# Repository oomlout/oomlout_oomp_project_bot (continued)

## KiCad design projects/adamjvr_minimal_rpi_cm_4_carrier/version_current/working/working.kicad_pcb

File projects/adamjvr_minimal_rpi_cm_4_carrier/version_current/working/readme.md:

# Minimal-RPi-CM-4-Carrier by adamjvr  
This is a harvested standardized copy of a project from github.  
The original project can be found at:  
https://github.com/adamjvr/Minimal-RPi-CM-4-Carrier  
Please consult that link for additional, details, files, and license information.  
Note: It was auto harvested and if the original repo had more than one board file or anything out of the ordinary the files here are likely not representative.

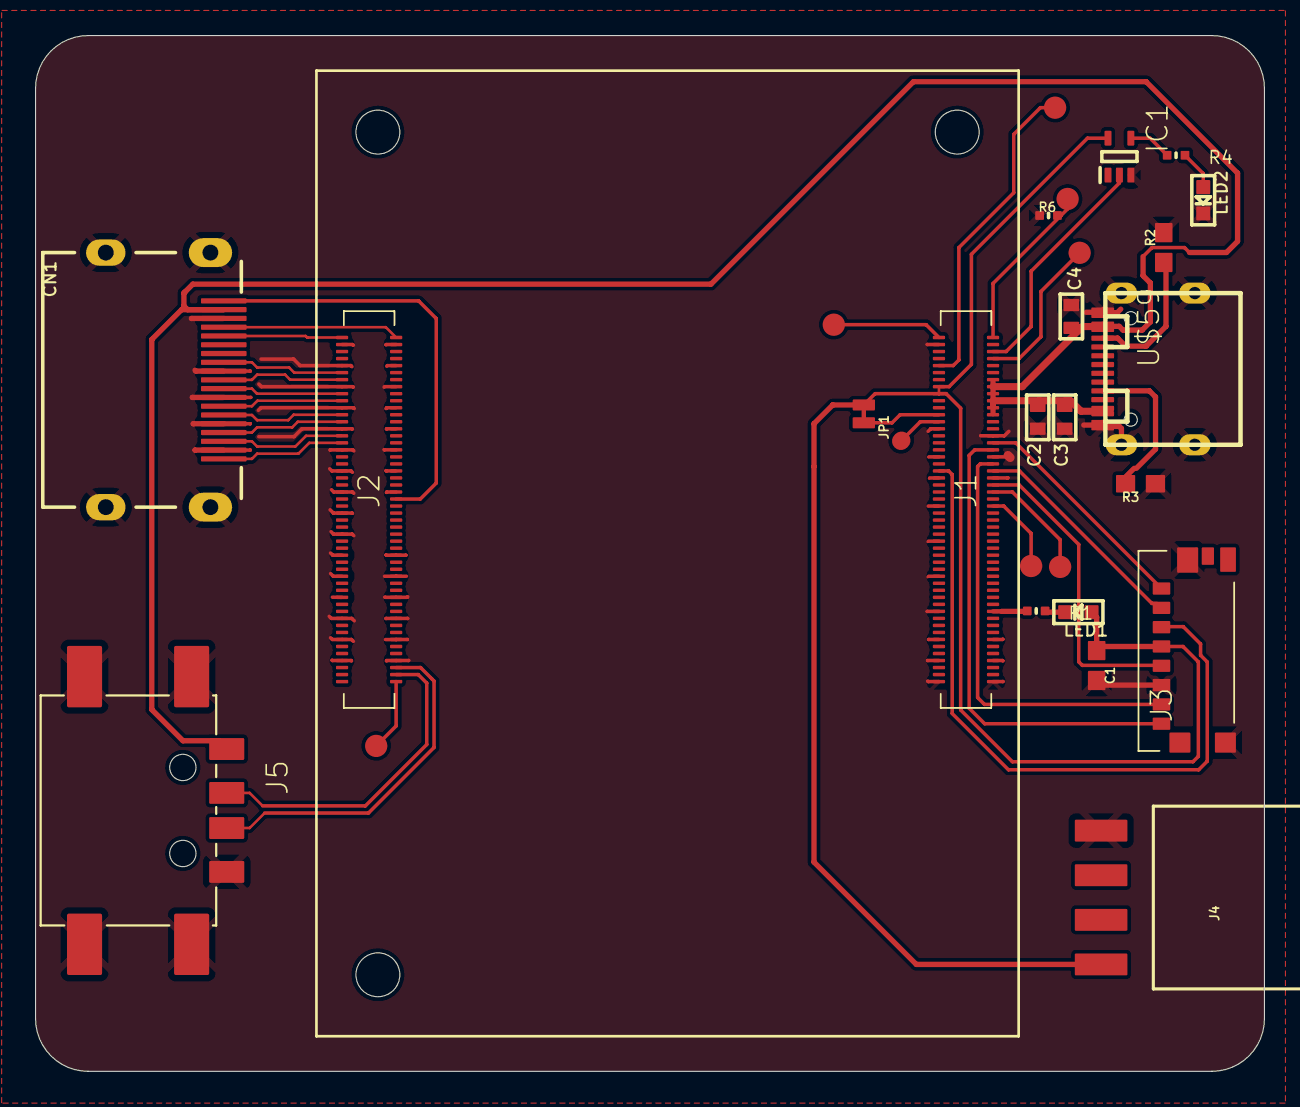
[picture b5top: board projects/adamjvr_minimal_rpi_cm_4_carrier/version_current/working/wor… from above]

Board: 2 copper layers, 70.0 x 59.0 mm, 30 parts (0 on the bottom side), 38 nets.

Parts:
@HOLE0, @HOLE1, @HOLE2: (no value)
C1: 10uF; 0603
C2, C3, C4: 0402
CN1: HDMI_MOLEX_47151-0001
IC1: MC74VHC1G14DFT1G; SOT65P210X110-5N
J1: P1-100; DF40C100DS04V51
J2: P101-200; DF40C100DS04V51
J3: 47571-0001
J4: 1X04_SMD_RA_FEMALE
J5: 629104190121
JP1: JUMPER-SMT_2_NC_TRACE_NO-SILK; SMT-JUMPER_2_NC_TRACE_NO-SILK
LED1, LED2: CHIPLED_0603
R1, R4: 1k; _0402MP
R2, R3: 5.1k; 0603
R6: 10k; _0402MP
TP1, TP2, TP3, TP4, TP5, TP6, TP7: TEST-POINT3X5; PAD.03X.05
U$59: TYPE-C-31-M-12; USB-TYPE-C_16PIN-MALE-TYPE-C-31-M-12

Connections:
1.8V: J1.88, J1.90
3.3V: C1.1, IC1.5, J1.84, J1.86, J3.P4, J4.1, JP1.1, LED1.A
5.0V: C2.1, C3.1, C4.1, CN1.18, J1.77, J1.79, J1.81, J1.83, J1.85, J1.87, J5.1, U$59.A4, U$59.A9, U$59.B4, U$59.B9
A0/CC2: R3.2, U$59.A5
A3/CC1: R2.1, U$59.B5
GLOBAL_EN: J1.99, R6.2, TP3.P$1
GND: C1.2, C2.2, C3.2, C4.2, CN1.2, CN1.5, CN1.8, CN1.11, CN1.17, CN1.P$1, CN1.P$2, CN1.P$3, CN1.P$4, IC1.3, J1.1, J1.2, J1.7, J1.8, J1.13, J1.14, J1.22, J1.23, J1.32, J1.33, J1.42, J1.43, J1.52, J1.53, J1.59, J1.60, J1.65, J1.66, J1.71, J1.74, J1.98, J2.7, J2.8, J2.13, J2.14, J2.19, J2.20, J2.25, J2.26, J2.31, J2.32, J2.37, J2.38, J2.44, J2.50, J2.55, J2.56, J2.61, J2.62, J2.67, J2.68, J2.73, J2.74, J2.79, J2.80, J2.85, J2.86, J2.91, J2.92, J2.97, J2.98, J3.G1, J3.G2, J3.G3, J3.P6, J4.4, J5.4, J5.SHELL, J5.SHELL1, J5.SHELL2, J5.SHELL3, LED2.C, R2.2, R3.1, R6.1, U$59.0, U$59.0-1, U$59.0-2, U$59.0-3, U$59.A1, U$59.A12, U$59.B1, U$59.B12
GPIO14: J1.55, J4.3, TP7.P$1
GPIO15: J1.51, J4.2, TP6.P$1
GPIO_VREF: J1.78, JP1.2
HDMI0_CK_N: CN1.12, J2.90
HDMI0_CK_P: CN1.10, J2.88
HDMI0_D0_N: CN1.9, J2.84
HDMI0_D0_P: CN1.7, J2.82
HDMI0_D1_N: CN1.6, J2.78
HDMI0_D1_P: CN1.4, J2.76
HDMI0_D2_N: CN1.3, J2.72
HDMI0_D2_P: CN1.1, J2.70
HDMI0_HOTPLUG: CN1.19, J2.53
HDMI0_SCL: CN1.15, J2.100
HDMI0_SDA: CN1.16, J2.99
unnamed: LED1.C, R1.2
unnamed: IC1.4, R4.1
unnamed: LED2.A, R4.2
N_EXTRST: J1.100, TP2.P$1
N_PWR_LED: IC1.2, J1.95
N_RPIBOOT: J1.93, TP4.P$1
PI_NLED_ACTIVITY: J1.21, R1.1
RUN_PG: J1.92, TP1.P$1
SD_CLK: J1.57, J3.P5
SD_CMD: J1.62, J3.P3
SD_DAT0: J1.63, J3.P7
SD_DAT1: J1.67, J3.P8
SD_DAT2: J1.69, J3.P1
SD_DAT3: J1.61, J3.P2
USB2_N: J2.3, J5.2
USB2_P: J2.5, J5.3
USBOTG_ID: J2.1, TP5.P$1

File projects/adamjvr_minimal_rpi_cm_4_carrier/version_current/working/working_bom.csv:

"Id";"Designator";"Footprint";"Quantity";"Designation";"Supplier and ref";
1;"R6";"_0402MP";1;"10k";;;
2;"R3,R2";"0603";2;"5.1k";;;
3;"J1";"DF40C100DS04V51";1;"P1-100";;;
4;"CN1";"HDMI_MOLEX_47151-0001";1;"";;;
5;"@HOLE0,@HOLE2,@HOLE1";"";3;"";;;
6;"R4,R1";"_0402MP";2;"1k";;;
7;"TP4,TP2,TP1,TP5,TP7,TP6,TP3";"PAD.03X.05";7;"TEST-POINT3X5";;;
8;"J3";"47571-0001";1;"47571-0001";;;
9;"IC1";"SOT65P210X110-5N";1;"MC74VHC1G14DFT1G";;;
10;"J2";"DF40C100DS04V51";1;"P101-200";;;
11;"C4,C2,C3";"0402";3;"";;;
12;"U$59";"USB-TYPE-C_16PIN-MALE-TYPE-C-31-M-12";1;"TYPE-C-31-M-12";;;
13;"LED2,LED1";"CHIPLED_0603";2;"";;;
14;"JP1";"SMT-JUMPER_2_NC_TRACE_NO-SILK";1;"JUMPER-SMT_2_NC_TRACE_NO-SILK";;;
15;"J4";"1X04_SMD_RA_FEMALE";1;"";;;
16;"J5";"629104190121";1;"";;;
17;"C1";"0603";1;"10uF";;;

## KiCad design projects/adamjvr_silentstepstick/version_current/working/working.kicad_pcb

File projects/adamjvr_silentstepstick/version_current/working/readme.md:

# OOMP Project  
## SilentStepStick  by adamjvr  
  
oomp key: oomp_projects_flat_adamjvr_silentstepstick  
(snippet of original readme)  
  
- SilentStepStick  
The Silent-Step-Stick is a Stepper Motor Driver Board for 2-Phase Motors based on [Trinamic](https://www.trinamic.com) Motor Drivers.  
  
* Hardware compatible with [StepStick](https://reprap.org/wiki/StepStick) and [Pololu A4988](https://www.pololu.com/product/1182)  
* [Trinamic](https://www.trinamic.com) stepper motor driver (chopper drive / constant current drive) with  
  * Automatic standby current reduction  
  * **microPlyer** - microstep interpolator for increased smoothness of microstepping  
  * **stealthChop** - for quiet operation and smooth motion  
  * **spreadCycle** - highly dynamic motor control chopper  
* Open-Source and released under the [Creative Commons Attribution Share-Alike License](https://creativecommons.org/licenses/by-sa/4.0/).  
* **[Documentation on learn.watterott.com](https://learn.watterott.com)**  
  
  full source readme at [readme_src.md](readme_src.md)  
  
source repo at: [https://github.com/adamjvr/SilentStepStick](https://github.com/adamjvr/SilentStepStick)  
## Board  

## Schematic  

[schematic pdf](working_schematic.pdf)  
## Images

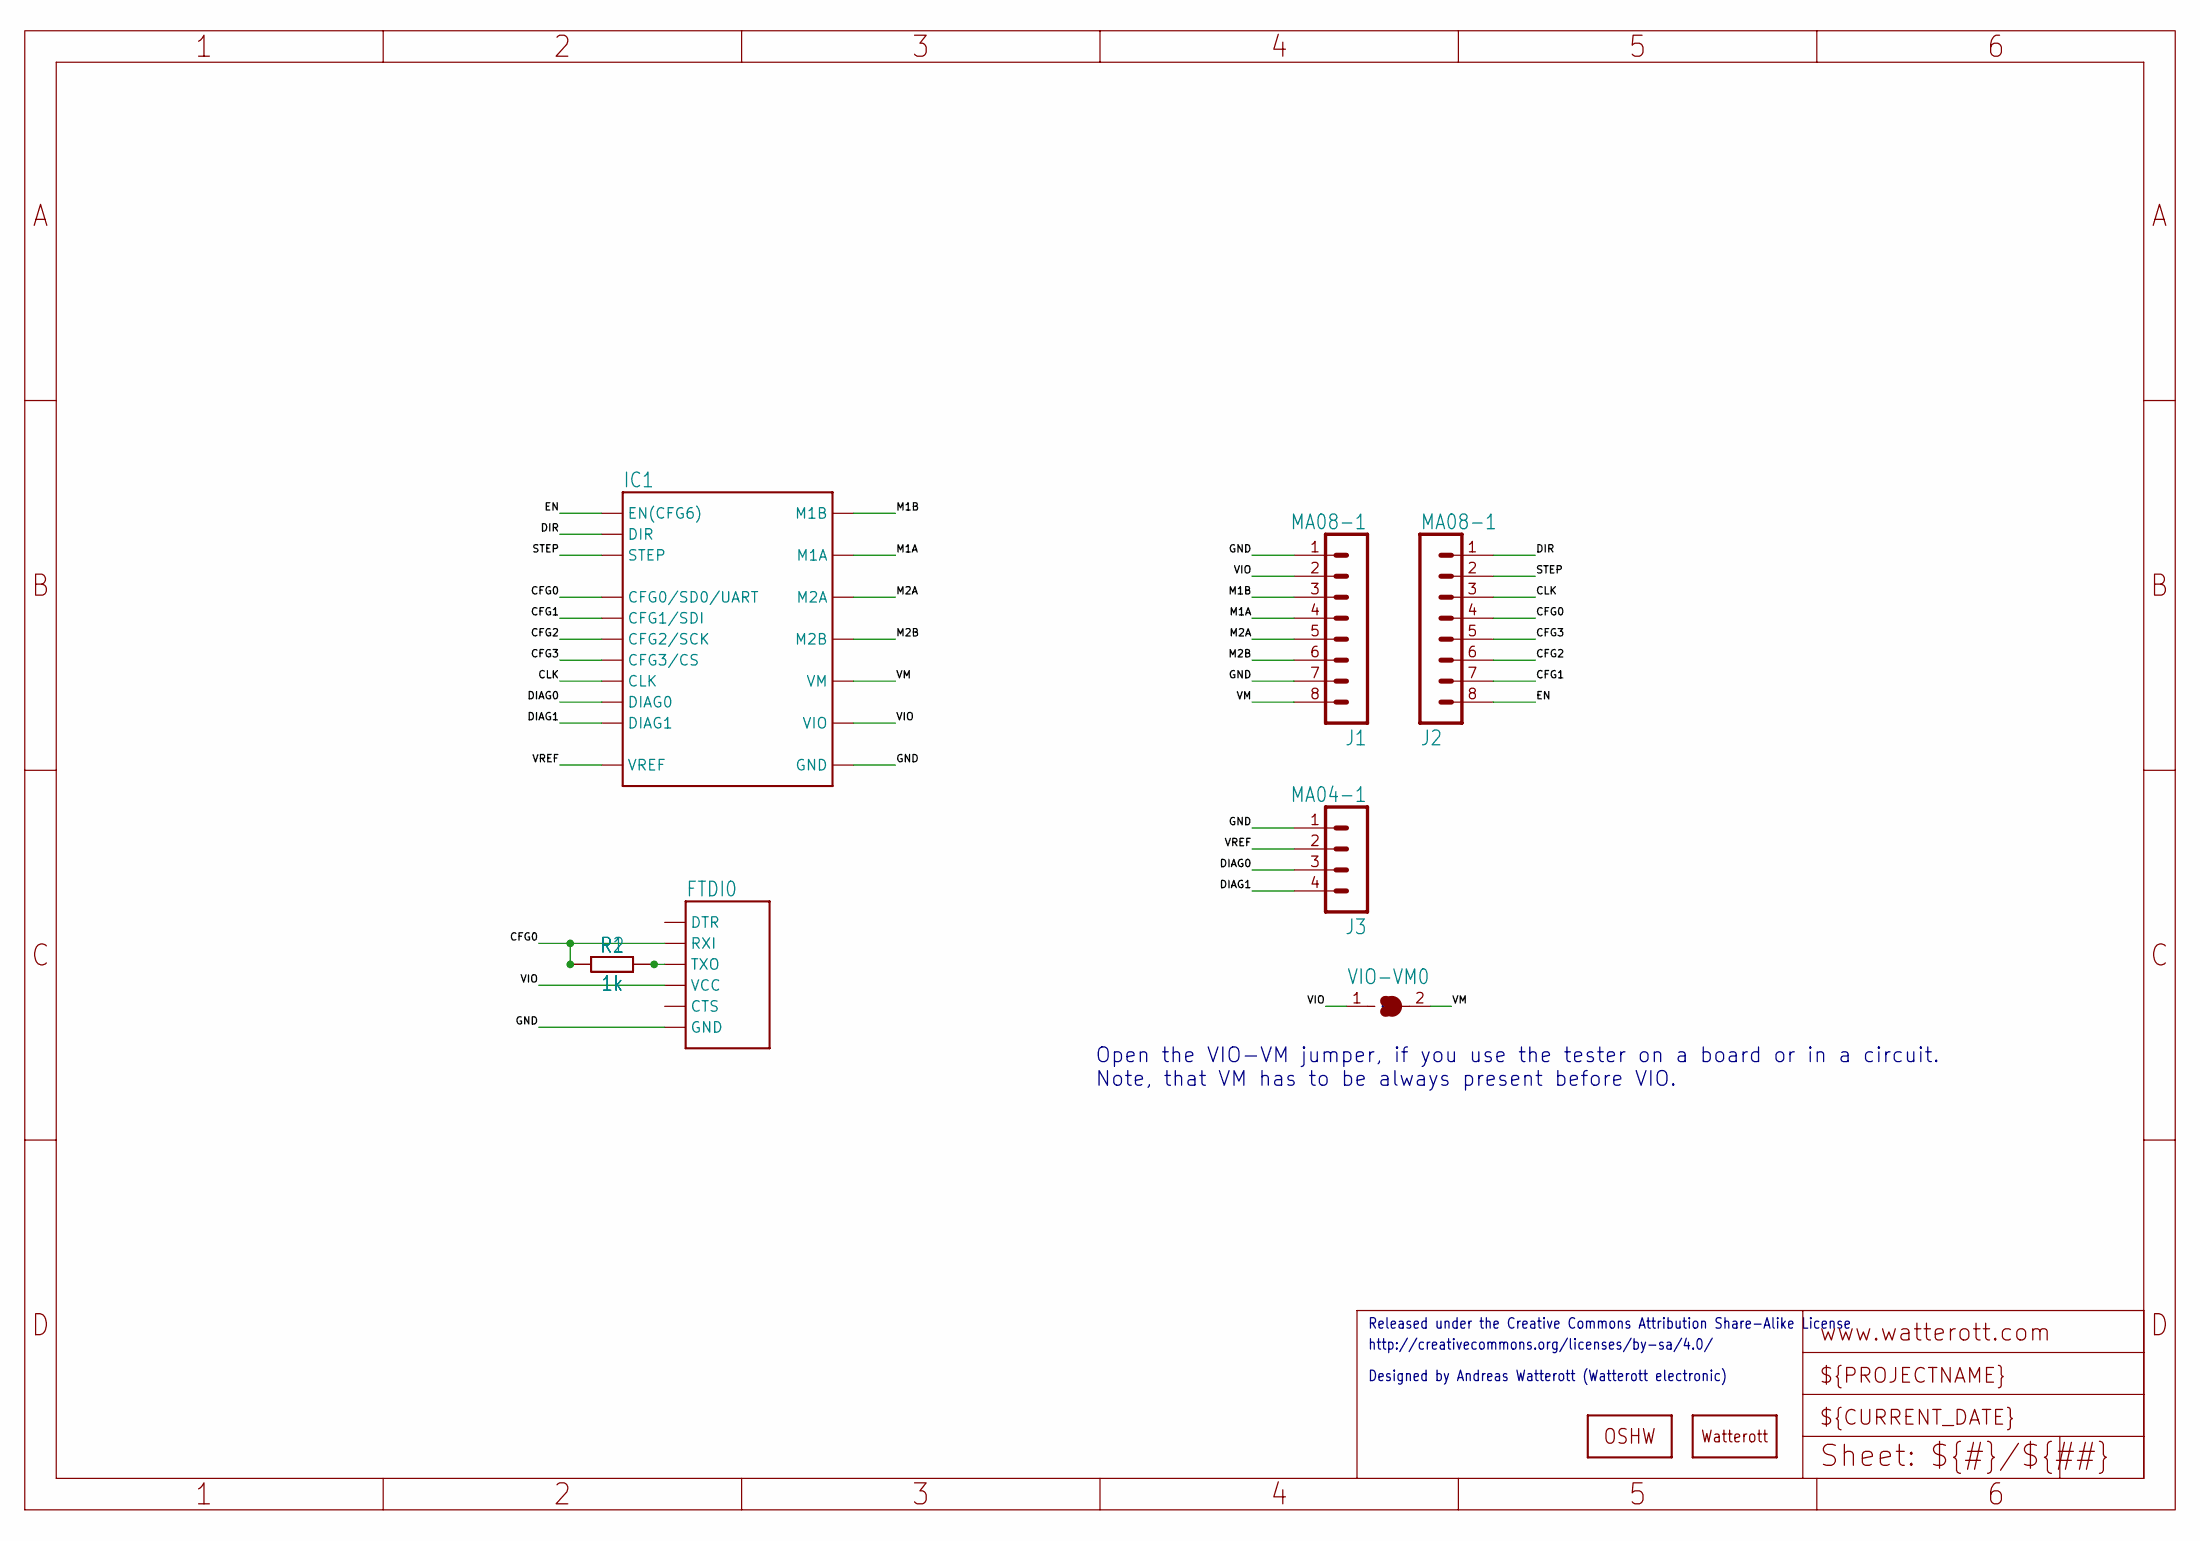
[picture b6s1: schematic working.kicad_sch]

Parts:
FTDI0: FTDI
IC1: STEPSTICK-TP; STEPSTICK_TP
J1, J2: MA08-1
J3: MA04-1
LOGO1: OSHW_LOGOX0070; OSHW_6X70
LOGO2: LOGO-S_PLACE_S; SPARK_TPLACE_S
R1: 1k; R0207_7
R2: 1k; C0805
VIO-VM0: JUMPER2-0603-NC; JUMPER2-0603_NC

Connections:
CFG0: FTDI0.5-RXI (RXI), IC1.NC/CFG0 (CFG0/SD0/UART), J2.4, R1.1, R2.1
CFG1: IC1.CFG1 (CFG1/SDI), J2.7
CFG2: IC1.CFG2 (CFG2/SCK), J2.6
CFG3: IC1.CFG3 (CFG3/CS), J2.5
CLK: IC1.NC/CLK (CLK), J2.3
DIAG0: IC1.DIAG0, J3.3
DIAG1: IC1.DIAG1, J3.4
DIR: IC1.DIR, J2.1
EN: IC1.EN (EN(CFG6)), J2.8
GND: FTDI0.1-GND (GND), IC1.GND@1 (GND), IC1.GND@2 (GND), J1.1, J1.7, J3.1
M1A: IC1.M1A, J1.4
M1B: IC1.M1B, J1.3
M2A: IC1.M2A, J1.5
M2B: IC1.M2B, J1.6
STEP: IC1.STEP, J2.2
TX: FTDI0.4-TXO (TXO), R1.2, R2.2
VIO: FTDI0.3-VCC (VCC), IC1.VIO, J1.2, VIO-VM0.1
VM: IC1.VM, J1.8, VIO-VM0.2
VREF: IC1.VREF, J3.2

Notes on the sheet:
Open the VIO-VM jumper, if you use the tester on a board or in a circuit. Note, that VM has to be always present before VIO.
http://creativecommons.org/licenses/by-sa/4.0/
Released under the Creative Commons Attribution Share-Alike License
Designed by Andreas Watterott (Watterott electronic)

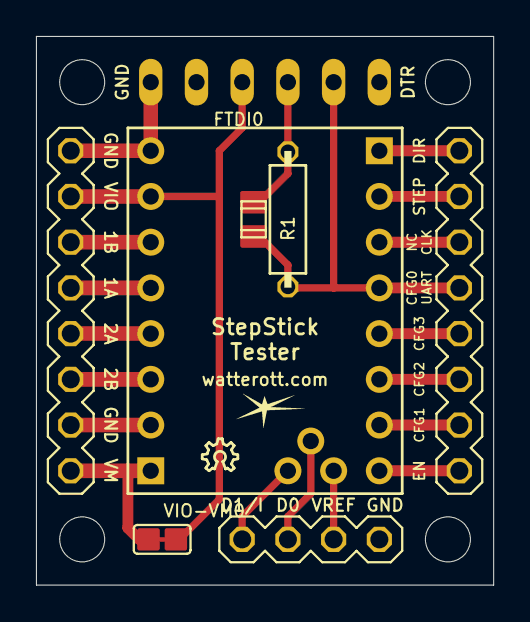
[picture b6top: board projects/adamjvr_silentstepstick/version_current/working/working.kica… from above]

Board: 2 copper layers, 25.4 x 30.5 mm, 14 parts (0 on the bottom side), 19 nets.

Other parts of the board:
@HOLE0, @HOLE1, @HOLE2, @HOLE3: (no value)

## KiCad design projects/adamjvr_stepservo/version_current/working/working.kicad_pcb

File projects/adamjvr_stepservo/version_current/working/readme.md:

# OOMP Project  
## StepServo  by adamjvr  
  
oomp key: oomp_projects_flat_adamjvr_stepservo  
(snippet of original readme)  
  
- StepServo  
  
Check out the wiki here: http://reprap.org/wiki/StepServo (under construction)  
  
A single channel step/direction/enable/endstop to DC quadrature encoder converter for use with 3D printers or CNC machines. So, basically, a single channel version of my other board, RAMPSSB (https://github.com/SZiv/RAMPSSB), and many of the rules that apply there, apply here. The firmware is identical.  
  
Uses an L298N DC motor driver stacked on standoffs as a driver, and an Arduino Pro Micro as a processor. Designed to need only an arduino Pro Micro, a L298N, some standoffs, an LED, a resistor, a 3mm terminal block, and a bunch of header. Can be assembled easily on your own.  
  
  full source readme at [readme_src.md](readme_src.md)  
  
source repo at: [https://github.com/adamjvr/StepServo](https://github.com/adamjvr/StepServo)  
## Board  

## Schematic  

[schematic pdf](working_schematic.pdf)  
## Images

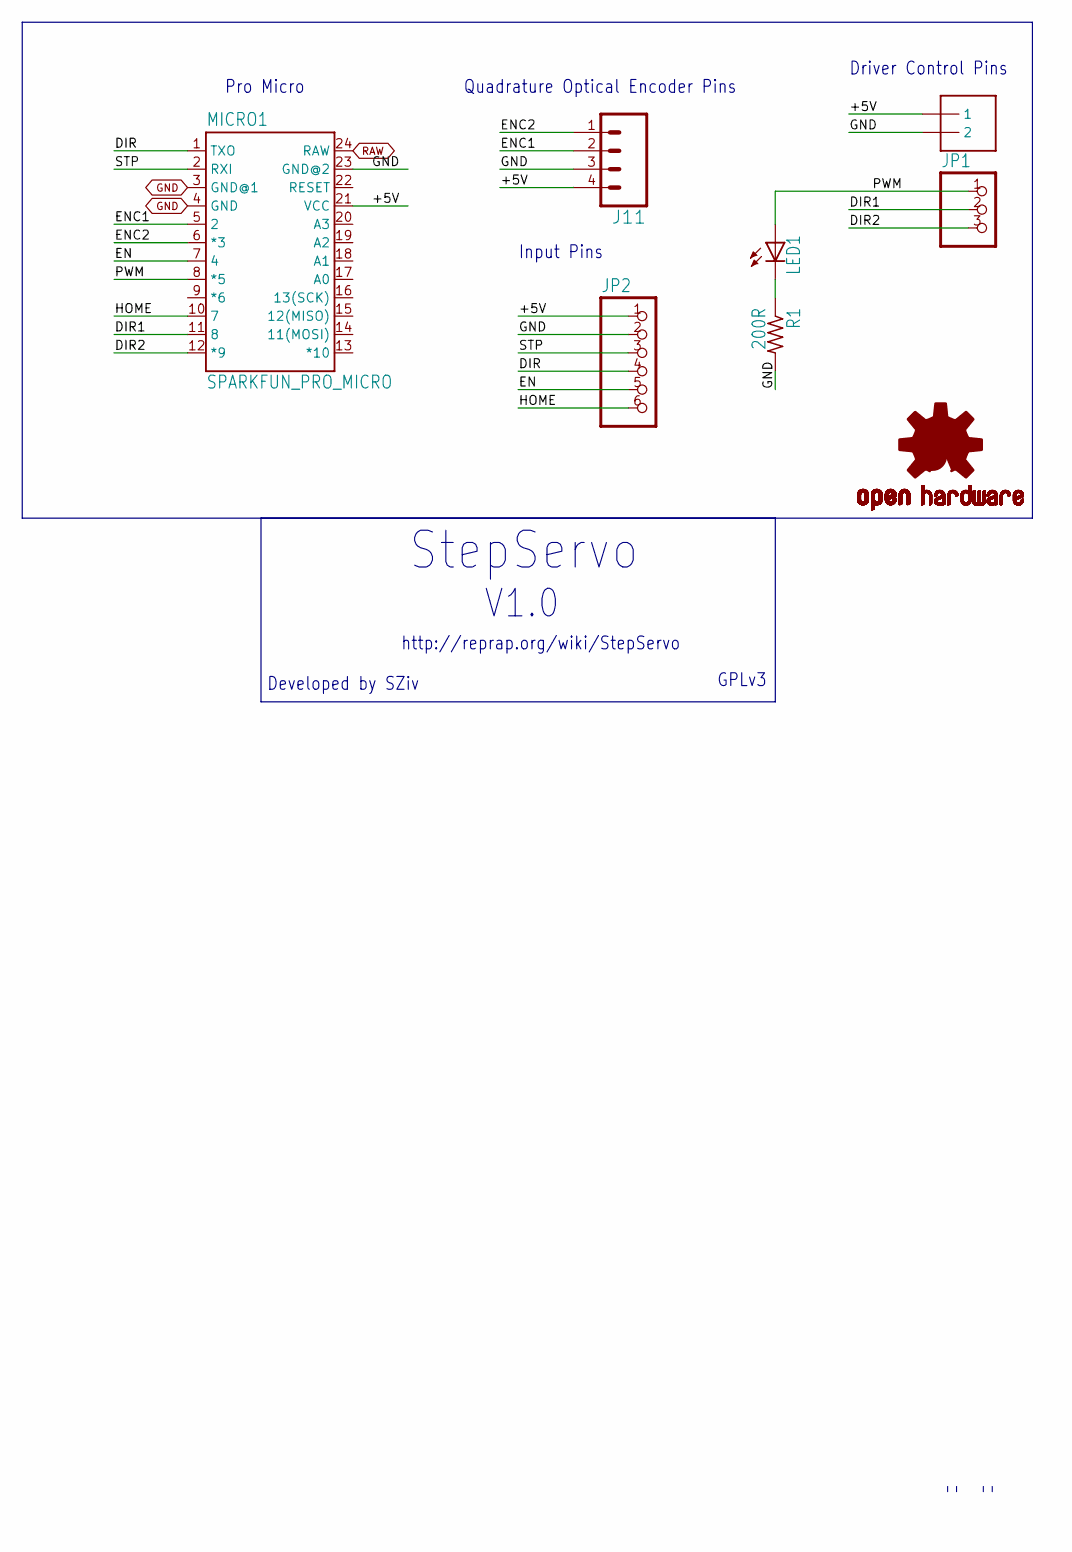
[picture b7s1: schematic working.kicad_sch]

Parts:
J2: 1X2-3.5MM
J11: CONN_04; 1X04
JP1: PINHD-1X3; 1X03
JP2: PINHD-1X6; 1X06
LED1: LED3MM
LOGO1: OSHW-LOGOL; OSHW-LOGO-L
MICRO1: SPARKFUN_PRO_MICRO
R1: 200R; 0207_7

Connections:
+5V: J2.1, J11.4, JP2.1, MICRO1.21 (VCC)
DIR: JP2.4, MICRO1.1 (TXO)
DIR1: JP1.2, MICRO1.11 (8)
DIR2: JP1.3, MICRO1.12 (*9)
EN: JP2.5, MICRO1.7 (4)
ENC1: J11.2, MICRO1.5 (2)
ENC2: J11.1, MICRO1.6 (*3)
GND: J2.2, J11.3, JP2.2, MICRO1.3 (GND@1), MICRO1.4 (GND), MICRO1.23 (GND@2), R1.2
HOME: JP2.6, MICRO1.10 (7)
unnamed: LED1.K (C), R1.1
PWM: JP1.1, LED1.A, MICRO1.8 (*5)
RAW: MICRO1.24 (RAW)
STP: JP2.3, MICRO1.2 (RXI)

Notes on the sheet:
Quadrature Optical Encoder Pins
V1.0
http://reprap.org/wiki/StepServo
Input Pins
Driver Control Pins
GPLv3
Developed by SZiv
" "
Pro Micro
StepServo

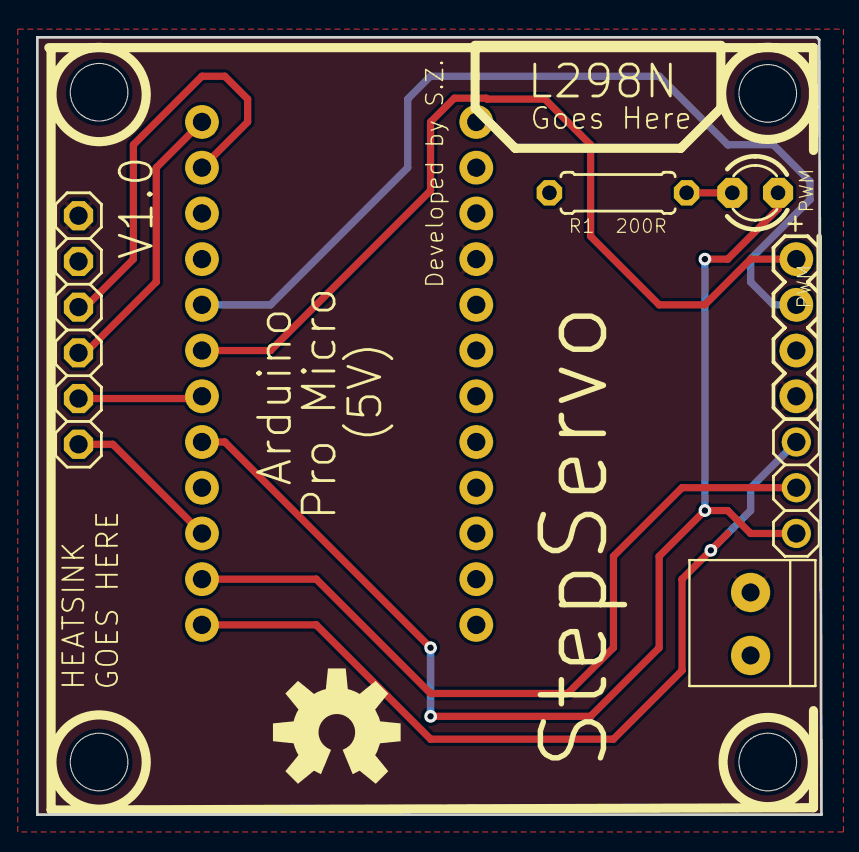
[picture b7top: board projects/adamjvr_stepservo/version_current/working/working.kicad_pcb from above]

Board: 2 copper layers, 43.6 x 43.2 mm, 12 parts (0 on the bottom side), 12 nets.

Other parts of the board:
@HOLE0, @HOLE1, @HOLE2, @HOLE3: (no value)

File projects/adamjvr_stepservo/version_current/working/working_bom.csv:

"Id";"Designator";"Footprint";"Quantity";"Designation";"Supplier and ref";
1;"LED1";"LED3MM";1;"";;;
2;"JP1";"1X03";1;"";;;
3;"LOGO1";"OSHW-LOGO-L";1;"OSHW-LOGOL";;;
4;"@HOLE3,@HOLE1,@HOLE2,@HOLE0";"";4;"";;;
5;"JP2";"1X06";1;"";;;
6;"J11";"1X04";1;"";;;
7;"R1";"0207_7";1;"200R";;;
8;"MICRO1";"SPARKFUN_PRO_MICRO";1;"SPARKFUN_PRO_MICRO";;;
9;"J2";"1X2-3.5MM";1;"1X2-3.5MM";;;

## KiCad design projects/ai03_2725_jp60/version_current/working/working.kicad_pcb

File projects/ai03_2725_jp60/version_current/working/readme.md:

# JP60 by ai03-2725  
This is a harvested standardized copy of a project from github.  
The original project can be found at:  
https://github.com/ai03-2725/JP60  
Please consult that link for additional, details, files, and license information.  
Note: It was auto harvested and if the original repo had more than one board file or anything out of the ordinary the files here are likely not representative.

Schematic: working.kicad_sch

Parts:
D1, D2, D3, D4, D5, D6, D7, D8, D9, D10, D11, D12, D13, D14, D15, D16, D17, D18, D19, D20, D21, D22, D23, D24, D25, D26, D27, D28, D29, D30, D31, D33, D34, D35, D36, D38, D39, D40, D41, D42, D44, D45, D46, D47, D49, D50, D51, D52, D54, D55, D56, D57, D59, D60, D61, D62, D63, D65, D66, D67, D70, D71, D72, D74: SOD-123; D_SOD-123
K_#0_1, K_#1, K_#2, K_#3, K_#4, K_#5, K_#6, K_#7, K_#8, K_#9: MX-NoLED; MXOnly-1U-Hotswap
K_'1: MX-NoLED; MXOnly-1U-Hotswap
K_,1: MX-NoLED; MXOnly-1U-Hotswap
K_-1: MX-NoLED; MXOnly-1U-Hotswap
K_.1: MX-NoLED; MXOnly-1U-Hotswap
K_/1: MX-NoLED; MXOnly-1U-Hotswap
K_;1: MX-NoLED; MXOnly-1U-Hotswap
K_=1: MX-NoLED; MXOnly-1U-Hotswap
K_A1: MX-NoLED; MXOnly-1U-Hotswap
K_B1: MX-NoLED; MXOnly-1U-Hotswap
K_C1: MX-NoLED; MXOnly-1U-Hotswap
K_CAPS1: MX-LED; MXOnly-1.75U-Hotswap
K_D1: MX-NoLED; MXOnly-1U-Hotswap
K_E1: MX-NoLED; MXOnly-1U-Hotswap
K_ENTER1: MX-NoLED; MXOnly-ISO-ROTATED-Hotswap
K_ESC1: MX-NoLED; MXOnly-1U-Hotswap
K_F1: MX-NoLED; MXOnly-1U-Hotswap
K_G1: MX-NoLED; MXOnly-1U-Hotswap
K_H1: MX-NoLED; MXOnly-1U-Hotswap
K_I1: MX-NoLED; MXOnly-1U-Hotswap
K_J1: MX-NoLED; MXOnly-1U-Hotswap
K_K1: MX-NoLED; MXOnly-1U-Hotswap
K_L1: MX-NoLED; MXOnly-1U-Hotswap
K_LALT1: MX-NoLED; MXOnly-1U-Hotswap
K_LCTRL1: MX-NoLED; MXOnly-1.25U-Hotswap
K_LGUI1: MX-NoLED; MXOnly-1U-Hotswap
K_LSFT1: MX-NoLED; MXOnly-2.25U-Hotswap
K_M1: MX-NoLED; MXOnly-1U-Hotswap
K_N1: MX-NoLED; MXOnly-1U-Hotswap
K_NFER1: MX-NoLED; MXOnly-1.25U-Hotswap
K_O1: MX-NoLED; MXOnly-1U-Hotswap
K_P1: MX-NoLED; MXOnly-1U-Hotswap
K_Q1: MX-NoLED; MXOnly-1U-Hotswap
K_R1: MX-NoLED; MXOnly-1U-Hotswap
K_RALT1: MX-NoLED; MXOnly-1U-Hotswap
K_RCTRL1: MX-NoLED; MXOnly-1.25U-Hotswap
K_RGUI1: MX-NoLED; MXOnly-1U-Hotswap
K_S1: MX-NoLED; MXOnly-1U-Hotswap
K_SBSPC1, K_SBSPC2: MX-NoLED; MXOnly-1U-Hotswap
K_SPC1: MX-NoLED; MXOnly-6U-Centered-Hotswap-ReversedStabilizers
K_SPC2: MX-NoLED; MXOnly-1U-Hotswap
K_SRSFT1: MX-NoLED; MXOnly-1U-Hotswap
K_SRSFT2: MX-NoLED; MXOnly-1.75U-Hotswap
K_T1: MX-NoLED; MXOnly-1U-Hotswap
K_TAB1: MX-NoLED; MXOnly-1.5U-Hotswap
K_U1: MX-NoLED; MXOnly-1U-Hotswap
K_V1: MX-NoLED; MXOnly-1U-Hotswap
K_W1: MX-NoLED; MXOnly-1U-Hotswap
K_X1: MX-NoLED; MXOnly-1U-Hotswap
K_XFER1: MX-NoLED; MXOnly-1.25U-Hotswap
K_Y1: MX-NoLED; MXOnly-1U-Hotswap
K_Z1: MX-NoLED; MXOnly-1U-Hotswap
K_[1: MX-NoLED; MXOnly-1U-Hotswap
K_\1: MX-NoLED; MXOnly-1U-Hotswap
K_]1: MX-NoLED; MXOnly-1U-Hotswap

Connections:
COL0: K_CAPS1.1, K_ESC1.2, K_LCTRL1.1, K_LSFT1.1, K_TAB1.1; also elsewhere on the board
COL1: K_#1.2, K_A1.1, K_LGUI1.1, K_Q1.1; also elsewhere on the board
COL2: K_#2.1, K_LALT1.1, K_S1.1, K_W1.1, K_Z1.1; also elsewhere on the board
COL3: K_#3.1, K_D1.1, K_E1.1, K_NFER1.1, K_X1.1; also elsewhere on the board
COL4: K_#4.1, K_C1.1, K_F1.1, K_R1.1; also elsewhere on the board
COL5: K_#5.1, K_G1.1, K_T1.1, K_V1.1; also elsewhere on the board
COL6: K_#6.1, K_B1.1, K_H1.2, K_Y1.1; also elsewhere on the board
COL7: K_#7.1, K_J1.1, K_N1.1, K_SPC1.1, K_SPC2.2, K_U1.1; also elsewhere on the board
COL8: K_#8.1, K_I1.1, K_K1.1, K_M1.1; also elsewhere on the board
COL9: K_#9.1, K_,1.1, K_L1.1, K_O1.1; also elsewhere on the board
COL10: K_#0_1.1, K_.1.1, K_;1.1, K_P1.1, K_XFER1.1; also elsewhere on the board
COL11: K_'1.1, K_-1.1, K_/1.1, K_RALT1.1, K_[1.1; also elsewhere on the board
COL12: K_=1.1, K_RGUI1.1, K_SBSPC2.1, K_SRSFT1.1, K_]1.1; also elsewhere on the board
COL13: K_ENTER1.1, K_RCTRL1.1, K_SBSPC1.1, K_SRSFT2.1, K_\1.1; also elsewhere on the board
unnamed: D1.2 (A), K_NFER1.2
unnamed: D2.2 (A), K_ESC1.1
unnamed: D3.2 (A), K_TAB1.2
unnamed: D4.2 (A), K_CAPS1.2
unnamed: D5.2 (A), K_LSFT1.2
unnamed: D6.2 (A), K_LCTRL1.2
unnamed: D7.2 (A), K_#1.1
unnamed: D8.2 (A), K_Q1.2
unnamed: D9.2 (A), K_A1.2
unnamed: D10.2 (A), K_XFER1.2
unnamed: D11.2 (A), K_LGUI1.2
unnamed: D12.2 (A), K_#2.2
unnamed: D13.2 (A), K_W1.2
unnamed: D14.2 (A), K_S1.2
unnamed: D15.2 (A), K_Z1.2
unnamed: D16.2 (A), K_LALT1.2
unnamed: D17.2 (A), K_SBSPC2.2
unnamed: D18.2 (A), K_#3.2
unnamed: D19.2 (A), K_E1.2
unnamed: D20.2 (A), K_D1.2
unnamed: D21.2 (A), K_X1.2
unnamed: D22.2 (A), K_SRSFT1.2
unnamed: D23.2 (A), K_#4.2
unnamed: D24.2 (A), K_R1.2
unnamed: D25.2 (A), K_F1.2
unnamed: D26.2 (A), K_C1.2
unnamed: D27.2 (A), K_RGUI1.2
unnamed: D28.2 (A), K_#5.2
unnamed: D29.2 (A), K_T1.2
unnamed: D30.2 (A), K_G1.2
unnamed: D31.2 (A), K_V1.2
unnamed: D33.2 (A), K_#6.2
unnamed: D34.2 (A), K_Y1.2
unnamed: D35.2 (A), K_H1.1
unnamed: D36.2 (A), K_B1.2
unnamed: D38.2 (A), K_#7.2
unnamed: D39.2 (A), K_U1.2
unnamed: D40.2 (A), K_J1.2
unnamed: D41.2 (A), K_N1.2
unnamed: D42.2 (A), K_SPC1.2, K_SPC2.1
unnamed: D44.2 (A), K_#8.2
unnamed: D45.2 (A), K_I1.2
unnamed: D46.2 (A), K_K1.2
unnamed: D47.2 (A), K_M1.2
unnamed: D49.2 (A), K_#9.2
unnamed: D50.2 (A), K_O1.2
unnamed: D51.2 (A), K_L1.2
unnamed: D52.2 (A), K_,1.2
unnamed: D54.2 (A), K_#0_1.2
unnamed: D55.2 (A), K_P1.2
unnamed: D56.2 (A), K_;1.2
unnamed: D57.2 (A), K_.1.2
unnamed: D59.2 (A), K_-1.2
unnamed: D60.2 (A), K_[1.2
unnamed: D61.2 (A), K_'1.2
unnamed: D62.2 (A), K_/1.2
unnamed: D63.2 (A), K_RALT1.2
unnamed: D65.2 (A), K_=1.2
unnamed: D66.2 (A), K_]1.2
unnamed: D67.2 (A), K_SRSFT2.2
unnamed: D70.2 (A), K_SBSPC1.2
unnamed: D71.2 (A), K_\1.2
unnamed: D72.2 (A), K_ENTER1.2
unnamed: D74.2 (A), K_RCTRL1.2
ROW0: D2.1 (K), D7.1 (K), D12.1 (K), D18.1 (K), D23.1 (K), D28.1 (K), D33.1 (K), D38.1 (K), D44.1 (K), D49.1 (K), D54.1 (K), D59.1 (K), D65.1 (K), D70.1 (K); also elsewhere on the board
ROW1: D3.1 (K), D8.1 (K), D13.1 (K), D19.1 (K), D24.1 (K), D29.1 (K), D34.1 (K), D39.1 (K), D45.1 (K), D50.1 (K), D55.1 (K), D60.1 (K), D66.1 (K), D71.1 (K); also elsewhere on the board
ROW2: D4.1 (K), D9.1 (K), D14.1 (K), D17.1 (K), D20.1 (K), D25.1 (K), D30.1 (K), D35.1 (K), D40.1 (K), D46.1 (K), D51.1 (K), D56.1 (K), D61.1 (K), D72.1 (K); also elsewhere on the board
ROW3: D5.1 (K), D15.1 (K), D21.1 (K), D22.1 (K), D26.1 (K), D31.1 (K), D36.1 (K), D41.1 (K), D47.1 (K), D52.1 (K), D57.1 (K), D62.1 (K), D67.1 (K); also elsewhere on the board
ROW4: D1.1 (K), D6.1 (K), D10.1 (K), D11.1 (K), D16.1 (K), D27.1 (K), D42.1 (K), D63.1 (K), D74.1 (K); also elsewhere on the board

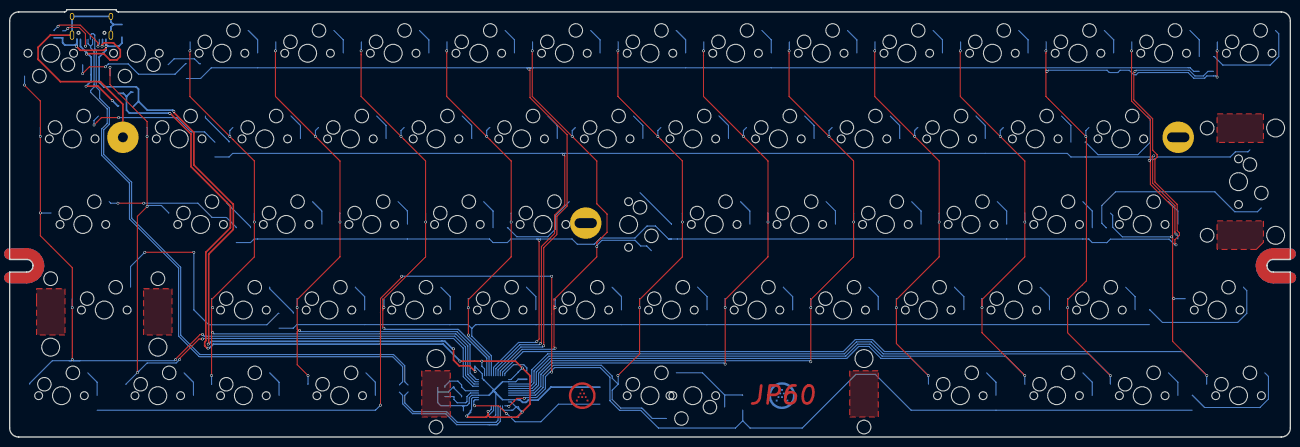
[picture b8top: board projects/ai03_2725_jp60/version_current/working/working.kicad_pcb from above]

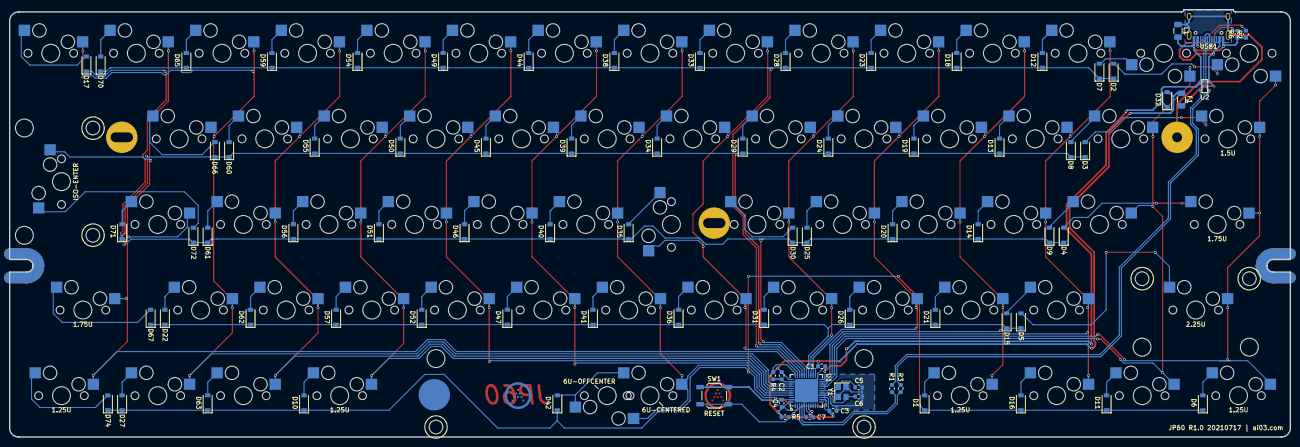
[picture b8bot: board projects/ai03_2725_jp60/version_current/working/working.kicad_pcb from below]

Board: 2 copper layers, 285.0 x 95.1 mm, 150 parts (85 on the bottom side), 98 nets.

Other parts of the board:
C1, C2, C3: 0.1uF; C_0603_1608Metric
C4: 10uF; C_0603_1608Metric
C5, C6: 22pF; C_0603_1608Metric
C7: 1uF; C_0603_1608Metric
D32: SMF6.0CA; D_SOD-123
F1: Polyfuse_Small; Fuse_1206_3216Metric
L1: 60R@100MHz; L_1206_3216Metric
R1, R3: 22; R_0603_1608Metric
R2, R6: 5.1k; R_0603_1608Metric
R4: 1k; R_0603_1608Metric
R5: 10k; R_0603_1608Metric
SW1: SW_Push; SW_SPST_TL3342
U1: ATmega32U4-MU; QFN-44-1EP_7x7mm_P0.5mm_EP5.2x5.2mm
U2: PRTR5V0U2X; SOT143B
USB1: HRO-TYPE-C-31-M-12; HRO-TYPE-C-31-M-12-Assembly
Y1: 16MHz; Crystal_SMD_3225-4Pin_3.2x2.5mm

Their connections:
+5V: C1.1, C2.1, C3.1, C4.1, D32.2, F1.1, R5.2, U1.2, U1.7, U1.14, U1.24, U1.34, U1.44
COL0: U1.20; also elsewhere on the board
COL1: U1.19; also elsewhere on the board
COL2: U1.21; also elsewhere on the board
COL3: U1.22; also elsewhere on the board
COL4: U1.25; also elsewhere on the board
COL5: U1.26; also elsewhere on the board
COL6: U1.31; also elsewhere on the board
COL7: U1.41; also elsewhere on the board
COL8: U1.40; also elsewhere on the board
COL9: U1.39; also elsewhere on the board
COL10: U1.38; also elsewhere on the board
COL11: U1.37; also elsewhere on the board
COL12: U1.36; also elsewhere on the board
COL13: U1.32; also elsewhere on the board
D+: R1.2, U2.2, USB1.6, USB1.8
D-: R3.2, U2.3, USB1.5, USB1.7
Earth: L1.1, USB1.13
GND: C1.2, C2.2, C3.2, C4.2, C5.2, C6.2, C7.1, D32.1, L1.2, R2.1, R4.1, R6.1, SW1.1, U1.5, U1.15, U1.23, U1.35, U1.43, U1.45, U2.1, USB1.1, USB1.12, Y1.2, Y1.4
unnamed: C5.1, U1.17, Y1.1
unnamed: C6.1, U1.16, Y1.3
unnamed: C7.2, U1.6
unnamed: R2.2, USB1.10
unnamed: R4.2, U1.33
unnamed: R5.1, SW1.2, U1.13
unnamed: R6.2, USB1.4
ROW0: U1.30; also elsewhere on the board
ROW1: U1.29; also elsewhere on the board
ROW2: U1.28; also elsewhere on the board
ROW3: U1.27; also elsewhere on the board
ROW4: U1.1; also elsewhere on the board
USB+: R1.1, U1.4
USB-: R3.1, U1.3
VCC: F1.2, U2.4, USB1.2, USB1.11

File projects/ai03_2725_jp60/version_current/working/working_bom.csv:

"Id";"Designator";"Footprint";"Quantity";"Designation";"Supplier and ref";
1;"K_.1,K_,1,K_#1,K_#2,K_#3,K_#4,K_#5,K_#6,K_#7,K_#8,K_#9,K_#0_1,K_'1,K_-1,K_/1,K_;1,K_[1,K_\1,K_]1,K_A1,K_B1,K_SBSPC1,K_C1,K_D1,K_E1,K_F1,K_G1,K_ESC1,K_H1,K_I1,K_J1,K_K1,K_L1,K_LALT1,K_M1,K_N1,K_O1,K_P1,K_R1,K_RALT1,K_S1,K_T1,K_U1,K_V1,K_X1,K_Y1,K_Z1,K_LGUI1,K_RGUI1,K_SRSFT1,K_SBSPC2,K_W1,K_Q1,K_=1,K_SPC2";"MXOnly-1U-Hotswap";55;"MX-NoLED";;;
2;"K_ENTER1";"MXOnly-ISO-ROTATED-Hotswap";1;"MX-NoLED";;;
3;"K_LCTRL1,K_RCTRL1,K_NFER1,K_XFER1";"MXOnly-1.25U-Hotswap";4;"MX-NoLED";;;
4;"K_LSFT1";"MXOnly-2.25U-Hotswap";1;"MX-NoLED";;;
5;"K_SRSFT2";"MXOnly-1.75U-Hotswap";1;"MX-NoLED";;;
6;"K_SPC1";"MXOnly-6U-Centered-Hotswap-ReversedStabilizers";1;"MX-NoLED";;;
7;"K_TAB1";"MXOnly-1.5U-Hotswap";1;"MX-NoLED";;;
8;"K_CAPS1";"MXOnly-1.75U-Hotswap";1;"MX-LED";;;
9;"G***,G***";"ai-ring-6mm-Combined";2;"LOGO";;;
10;"D2,D3,D4,D5,D6,D8,D12,D14,D15,D16,D18,D19,D20,D21,D23,D24,D25,D26,D28,D29,D31,D33,D34,D35,D36,D38,D39,D40,D41,D42,D44,D45,D46,D47,D49,D50,D51,D52,D54,D55,D56,D57,D59,D60,D61,D62,D63,D66,D67,D71,D72,D74,D70,D65,D11,D17,D22,D27,D13,D1,D10,D30,D9,D7";"D_SOD-123";64;"SOD-123";;;
11;"R4";"R_0603_1608Metric";1;"1k";;;
12;"C1,C2,C3";"C_0603_1608Metric";3;"0.1uF";;;
13;"R5";"R_0603_1608Metric";1;"10k";;;
14;"SW1";"SW_SPST_TL3342";1;"SW_Push";;;
15;"D32";"D_SOD-123";1;"SMF6.0CA";;;
16;"F1";"Fuse_1206_3216Metric";1;"Polyfuse_Small";;;
17;"L1";"L_1206_3216Metric";1;"60R@100MHz";;;
18;"R2,R6";"R_0603_1608Metric";2;"5.1k";;;
19;"U2";"SOT143B";1;"PRTR5V0U2X";;;
20;"USB1";"HRO-TYPE-C-31-M-12-Assembly";1;"HRO-TYPE-C-31-M-12";;;
21;"U1";"QFN-44-1EP_7x7mm_P0.5mm_EP5.2x5.2mm";1;"ATmega32U4-MU";;;
22;"Y1";"Crystal_SMD_3225-4Pin_3.2x2.5mm";1;"16MHz";;;
23;"C6,C5";"C_0603_1608Metric";2;"22pF";;;
24;"C4";"C_0603_1608Metric";1;"10uF";;;
25;"C7";"C_0603_1608Metric";1;"1uF";;;
26;"R1,R3";"R_0603_1608Metric";2;"22";;;
